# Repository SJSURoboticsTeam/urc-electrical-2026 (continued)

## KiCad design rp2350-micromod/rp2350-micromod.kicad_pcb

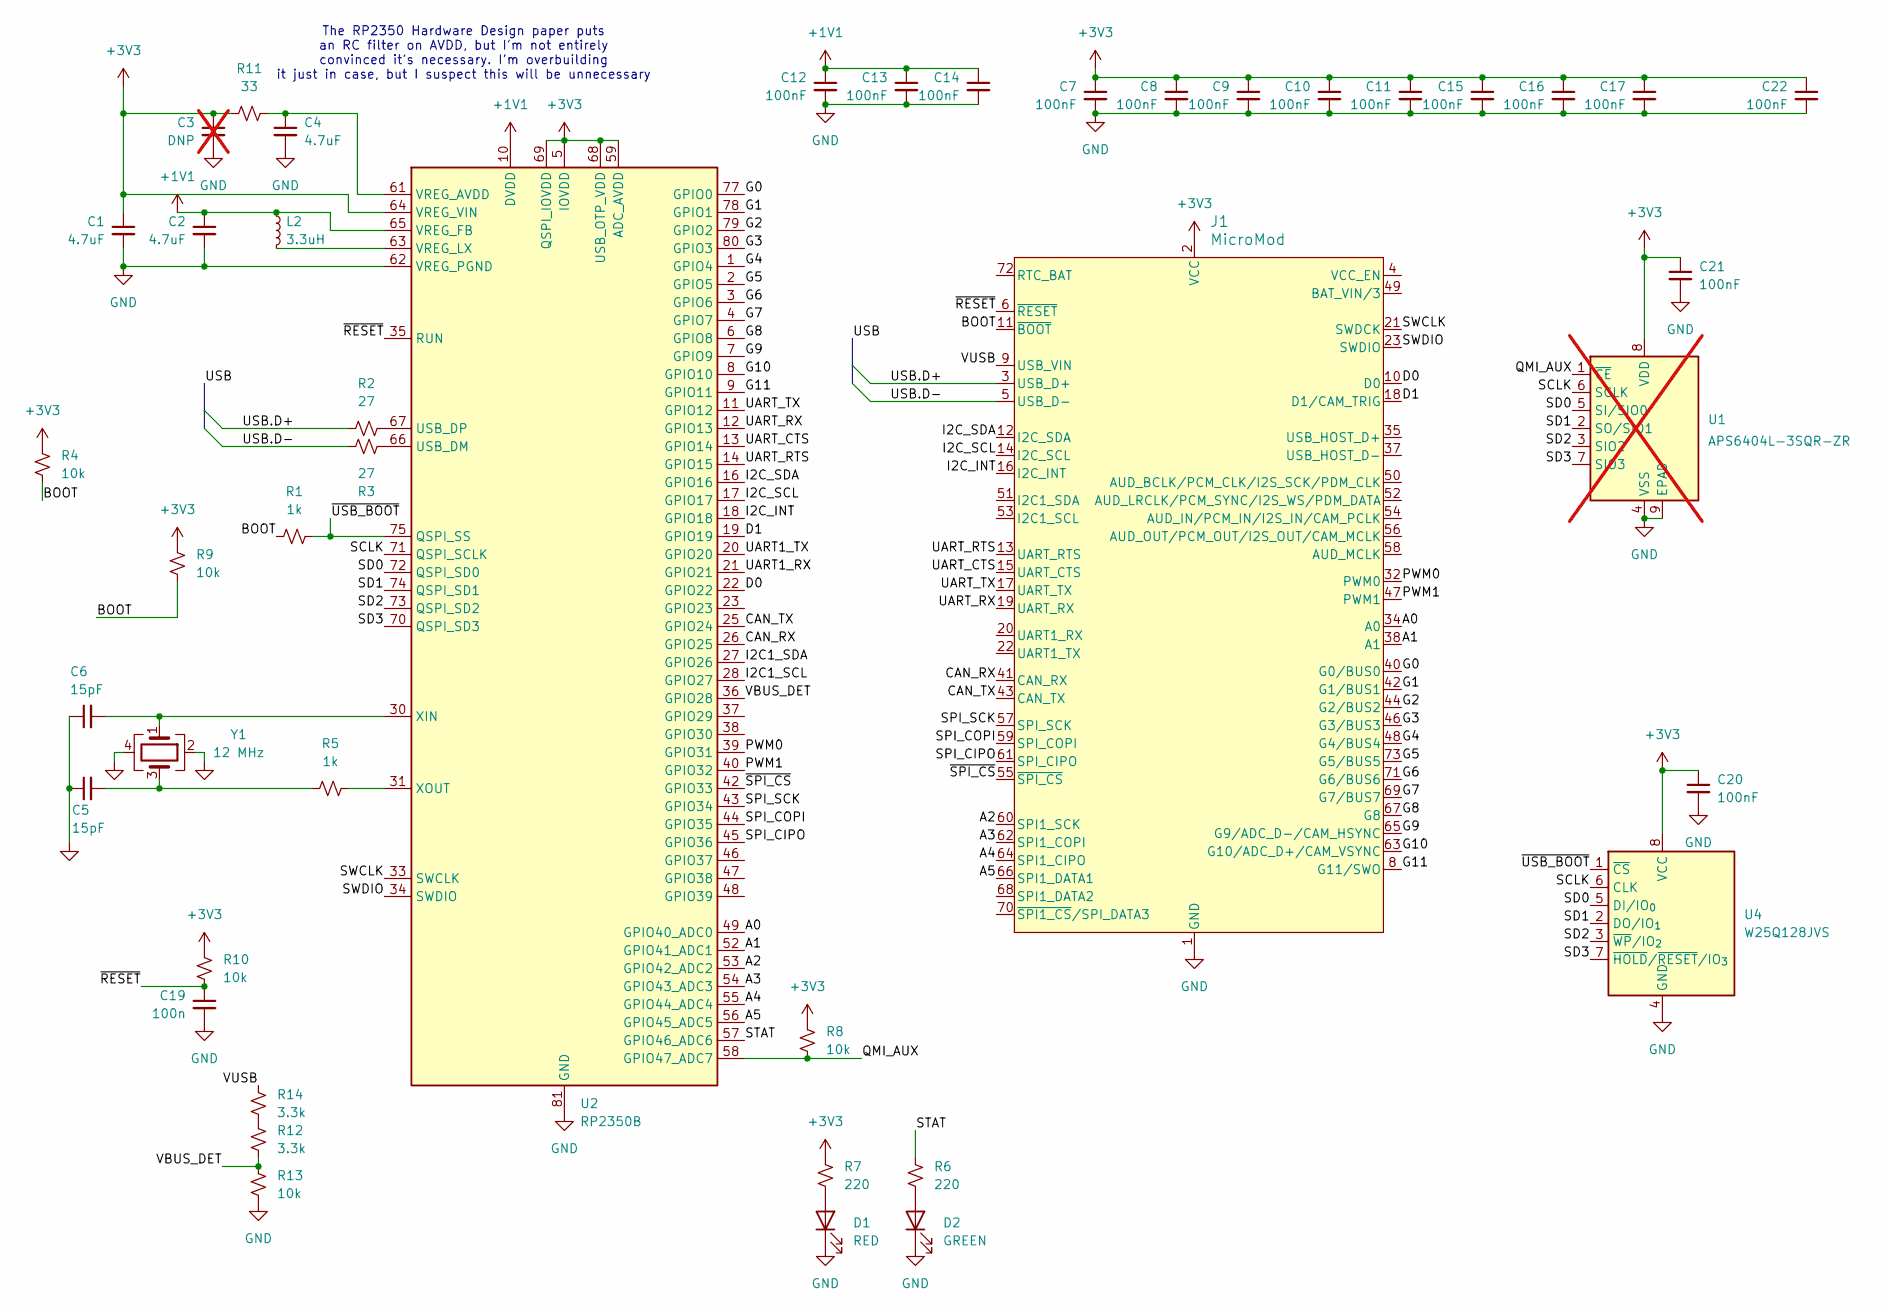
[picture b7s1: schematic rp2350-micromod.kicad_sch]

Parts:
C1, C2, C4: 4.7uF; C_0402_1005Metric
C3: DNP; C_0402_1005Metric; not fitted
C5, C6: 15pF; C_0402_1005Metric
C7, C8, C9, C10, C11, C12, C13, C14, C15, C16, C17, C20, C21, C22: 100nF; C_0402_1005Metric
C19: 100n; C_0402_1005Metric
D1: RED; LED_0603_1608Metric; JLCPCB Part C2286
D2: GREEN; LED_0603_1608Metric; JLCPCB Part C19171392
J1: MicroMod; M.2-CARD-E-22
L2: 3.3uH; L_0806_2016Metric; JLCPCB Part C42411119
R1, R5: 1k; R_0402_1005Metric
R2, R3: 27; R_0402_1005Metric
R4, R8, R9, R10, R13: 10k; R_0402_1005Metric
R6, R7: 220; R_0402_1005Metric; JLCPCB Part C1111
R11: 33; R_0402_1005Metric
R12, R14: 3.3k; R_0402_1005Metric
U1: APS6404L-3SQR-ZR; Winbond_USON-8-1EP_3x2mm_P0.5mm_EP0.2x1.6mm; not fitted
U2: RP2350B; QFN-80-1EP_10x10mm_P0.4mm_EP3.4x3.4mm; JLCPCB Part C42415655
U4: W25Q128JVS; SOIC-8_5.3x5.3mm_P1.27mm; JLCPCB Part C97521
Y1: 12 MHz; Crystal_SMD_Abracon_ABM8AIG-4Pin_3.2x2.5mm; JLCPCB Part C20625731

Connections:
+1V1: C2.1, C12.1, C13.1, C14.1, L2.1, U2.10 (DVDD), U2.32 (DVDD), U2.51 (DVDD), U2.65 (VREG_FB)
+3V3: C1.1, C3.1, C7.1, C8.1, C9.1, C10.1, C11.1, C15.1, C16.1, C17.1, C20.1, C21.1, C22.1, J1.2 (VCC), J1.74 (VCC), R4.2, R7.2, R8.2, R9.2, R10.2, R11.1, U1.8 (VDD), U2.5 (IOVDD), U2.15 (IOVDD), U2.24 (IOVDD), U2.29 (IOVDD), U2.41 (IOVDD), U2.50 (IOVDD), U2.59 (ADC_AVDD), U2.60 (IOVDD), U2.64 (VREG_VIN), U2.68 (USB_OTP_VDD), U2.69 (QSPI_IOVDD), U2.76 (IOVDD), U4.8 (VCC)
/A0: J1.34 (A0), U2.49 (GPIO40_ADC0)
/A1: J1.38 (A1), U2.52 (GPIO41_ADC1)
/A2: J1.60 (SPI1_SCK), U2.53 (GPIO42_ADC2)
/A3: J1.62 (SPI1_COPI), U2.54 (GPIO43_ADC3)
/A4: J1.64 (SPI1_CIPO), U2.55 (GPIO44_ADC4)
/A5: J1.66 (SPI1_DATA1), U2.56 (GPIO45_ADC5)
/BOOT: J1.11 (~BOOT), R1.1, R4.1, R9.1
/CAN_RX: J1.41 (CAN_RX), U2.26 (GPIO25)
/CAN_TX: J1.43 (CAN_TX), U2.25 (GPIO24)
/D0: J1.10 (D0), U2.22 (GPIO22)
/D1: J1.18 (D1/CAM_TRIG), U2.19 (GPIO19)
/G0: J1.40 (G0/BUS0), U2.77 (GPIO0)
/G1: J1.42 (G1/BUS1), U2.78 (GPIO1)
/G2: J1.44 (G2/BUS2), U2.79 (GPIO2)
/G3: J1.46 (G3/BUS3), U2.80 (GPIO3)
/G4: J1.48 (G4/BUS4), U2.1 (GPIO4)
/G5: J1.73 (G5/BUS5), U2.2 (GPIO5)
/G6: J1.71 (G6/BUS6), U2.3 (GPIO6)
/G7: J1.69 (G7/BUS7), U2.4 (GPIO7)
/G8: J1.67 (G8), U2.6 (GPIO8)
/G9: J1.65 (G9/ADC_D-/CAM_HSYNC), U2.7 (GPIO9)
/G10: J1.63 (G10/ADC_D+/CAM_VSYNC), U2.8 (GPIO10)
/G11: J1.8 (G11/SWO), U2.9 (GPIO11)
/I2C1_SCL: U2.28 (GPIO27)
/I2C1_SDA: U2.27 (GPIO26)
/I2C_INT: J1.16 (I2C_INT), U2.18 (GPIO18)
/I2C_SCL: J1.14 (I2C_SCL), U2.17 (GPIO17)
/I2C_SDA: J1.12 (I2C_SDA), U2.16 (GPIO16)
/PWM0: J1.32 (PWM0), U2.39 (GPIO31)
/PWM1: J1.47 (PWM1), U2.40 (GPIO32)
/QMI_AUX: R8.1, U1.1 (~CE), U2.58 (GPIO47_ADC7)
/SCLK: U1.6 (SCLK), U2.71 (QSPI_SCLK), U4.6 (CLK)
/SD0: U1.5 (SI/SIO0), U2.72 (QSPI_SD0), U4.5 (DI/IO_{0})
/SD1: U1.2 (SO/SIO1), U2.74 (QSPI_SD1), U4.2 (DO/IO_{1})
/SD2: U1.3 (SIO2), U2.73 (QSPI_SD2), U4.3 (~WP/IO_{2})
/SD3: U1.7 (SIO3), U2.70 (QSPI_SD3), U4.7 (~HOLD/~RESET/IO_{3})
/SPI_CIPO: J1.61 (SPI_CIPO), U2.45 (GPIO36)
/SPI_COPI: J1.59 (SPI_COPI), U2.44 (GPIO35)
/SPI_SCK: J1.57 (SPI_SCK), U2.43 (GPIO34)
/STAT: R6.2, U2.57 (GPIO46_ADC6)
/SWCLK: J1.21 (SWDCK), U2.33 (SWCLK)
/SWDIO: J1.23 (SWDIO), U2.34 (SWDIO)
/UART1_RX: U2.21 (GPIO21)
/UART1_TX: U2.20 (GPIO20)
/UART_CTS: J1.15 (UART_CTS), U2.13 (GPIO14)
/UART_RTS: J1.13 (UART_RTS), U2.14 (GPIO15)
/UART_RX: J1.19 (UART_RX), U2.12 (GPIO13)
/UART_TX: J1.17 (UART_TX), U2.11 (GPIO12)
/USB.D+: J1.3 (USB_D+), R2.1
/USB.D-: J1.5 (USB_D-), R3.1
/VBUS_DET: R12.1, R13.2, U2.36 (GPIO28)
/VUSB: J1.9 (USB_VIN), R14.2
/~RESET: C19.1, J1.6 (~RESET), R10.1, U2.35 (RUN)
/~SPI_CS: J1.55 (~SPI_CS), U2.42 (GPIO33)
/~USB_BOOT: R1.2, U2.75 (QSPI_SS), U4.1 (~CS)
GND: C1.2, C2.2, C3.2, C4.2, C5.1, C6.1, C7.2, C8.2, C9.2, C10.2, C11.2, C12.2, C13.2, C14.2, C15.2, C16.2, C17.2, C19.2, C20.2, C21.2, C22.2, D1.1 (K), D2.1 (K), J1.1 (GND), J1.7 (GND), J1.33 (GND), J1.36 (GND), J1.39 (GND), J1.45 (GND), J1.75 (GND), J1.S1 (GND), J1.S2 (GND), J1.S3 (GND), R13.1, U1.4 (VSS), U1.9 (EPAD), U2.62 (VREG_PGND), U2.81 (GND), U4.4 (GND), Y1.2, Y1.4
unnamed: C5.2, R5.1, Y1.3
unnamed: D1.2 (A), R7.1
unnamed: D2.2 (A), R6.1
unnamed: R12.2, R14.1
unnamed: R3.2, U2.66 (USB_DM)
unnamed: R2.2, U2.67 (USB_DP)
unnamed: C4.1, R11.2, U2.61 (VREG_AVDD)
unnamed: L2.2, U2.63 (VREG_LX)
unnamed: C6.2, U2.30 (XIN), Y1.1
unnamed: R5.2, U2.31 (XOUT)

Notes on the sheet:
The RP2350 Hardware Design paper puts an RC filter on AVDD, but I'm not entirely convinced it's necessary. I'm overbuilding it just in case, but I suspect this will be unnecessary

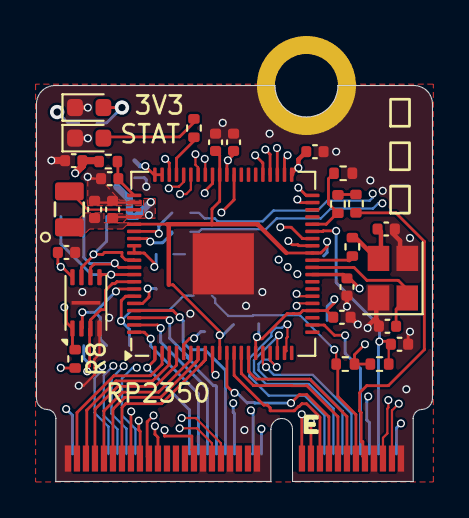
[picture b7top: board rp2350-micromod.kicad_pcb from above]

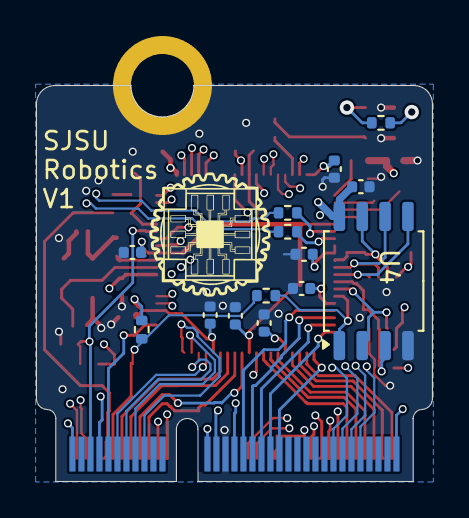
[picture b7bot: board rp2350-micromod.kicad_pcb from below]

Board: 4 copper layers, 22.0 x 22.0 mm, 43 parts (14 on the bottom side), 64 nets.

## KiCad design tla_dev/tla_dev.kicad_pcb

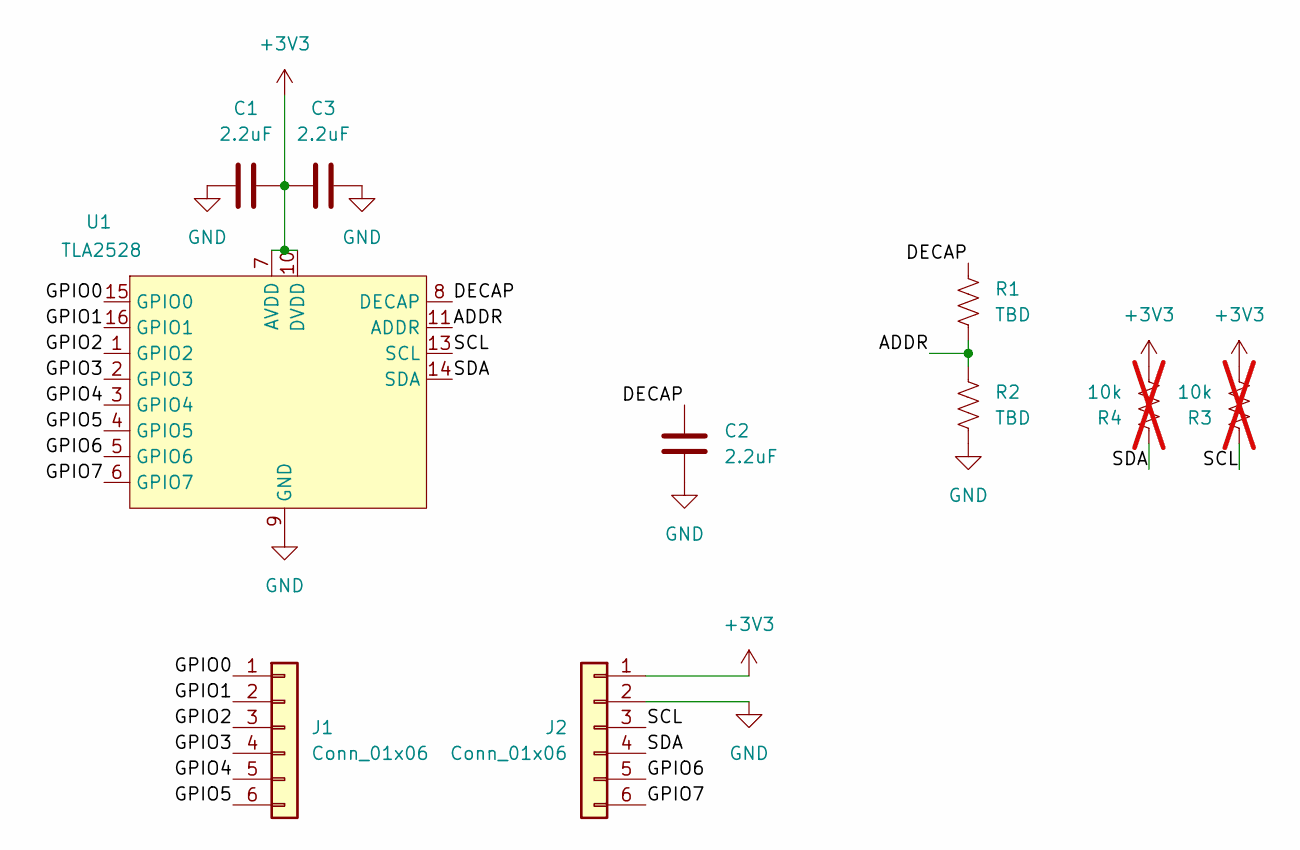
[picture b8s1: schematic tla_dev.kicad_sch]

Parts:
C1, C2, C3: 2.2uF; C_0603_1608Metric
J1, J2: Conn_01x06; PinHeader_1x06_P2.54mm_Vertical
R1, R2: TBD; R_0603_1608Metric
R3, R4: 10k; R_0603_1608Metric; not fitted
U1: TLA2528; QFN-16-1EP_3x3mm_P0.5mm_EP1.7x1.7mm

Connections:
+3V3: C1.2, C3.2, J2.1, R3.2, R4.2, U1.7 (AVDD), U1.10 (DVDD)
/ADDR: R1.2, R2.1, U1.11 (ADDR)
/DECAP: C2.2, R1.1, U1.8 (DECAP)
/GPIO0: J1.1, U1.15 (GPIO0)
/GPIO1: J1.2, U1.16 (GPIO1)
/GPIO2: J1.3, U1.1 (GPIO2)
/GPIO3: J1.4, U1.2 (GPIO3)
/GPIO4: J1.5, U1.3 (GPIO4)
/GPIO5: J1.6, U1.4 (GPIO5)
/GPIO6: J2.5, U1.5 (GPIO6)
/GPIO7: J2.6, U1.6 (GPIO7)
/SCL: J2.3, R3.1, U1.13 (SCL)
/SDA: J2.4, R4.1, U1.14 (SDA)
GND: C1.1, C2.1, C3.1, J2.2, R2.2, U1.9 (GND), U1.17 (GND)

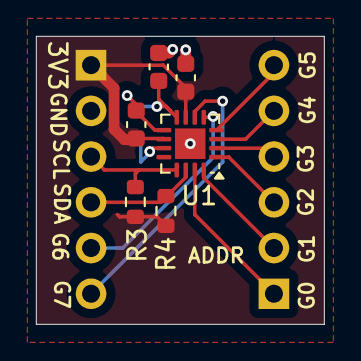
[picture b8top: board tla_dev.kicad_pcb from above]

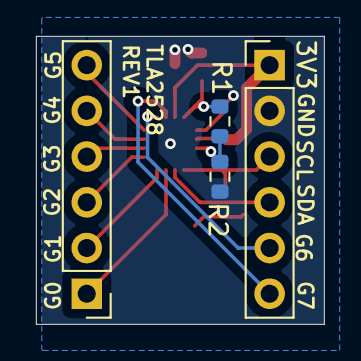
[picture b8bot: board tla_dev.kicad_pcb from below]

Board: 2 copper layers, 16.0 x 16.0 mm, 10 parts (4 on the bottom side), 14 nets.
